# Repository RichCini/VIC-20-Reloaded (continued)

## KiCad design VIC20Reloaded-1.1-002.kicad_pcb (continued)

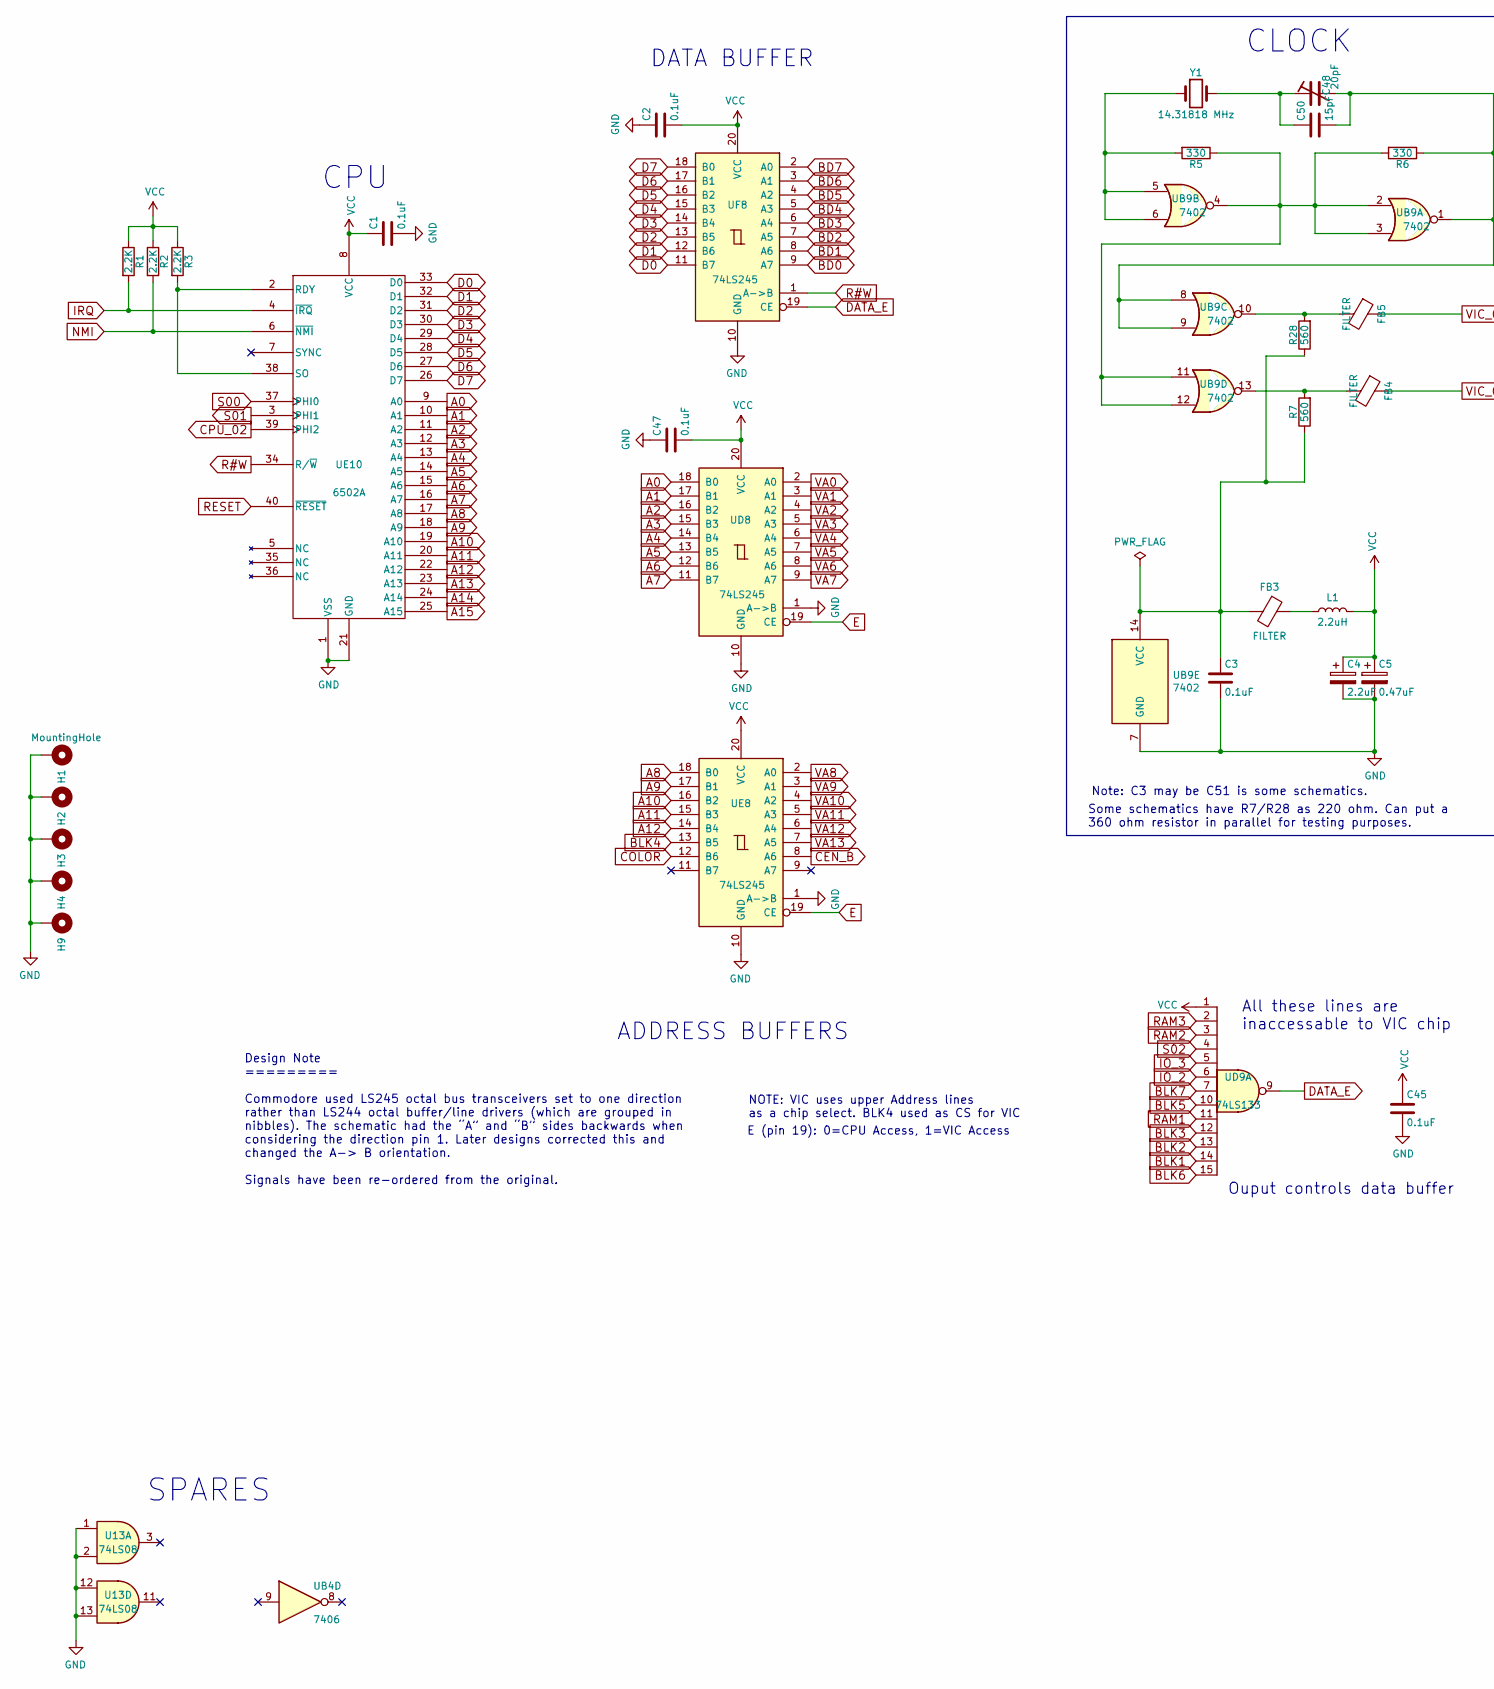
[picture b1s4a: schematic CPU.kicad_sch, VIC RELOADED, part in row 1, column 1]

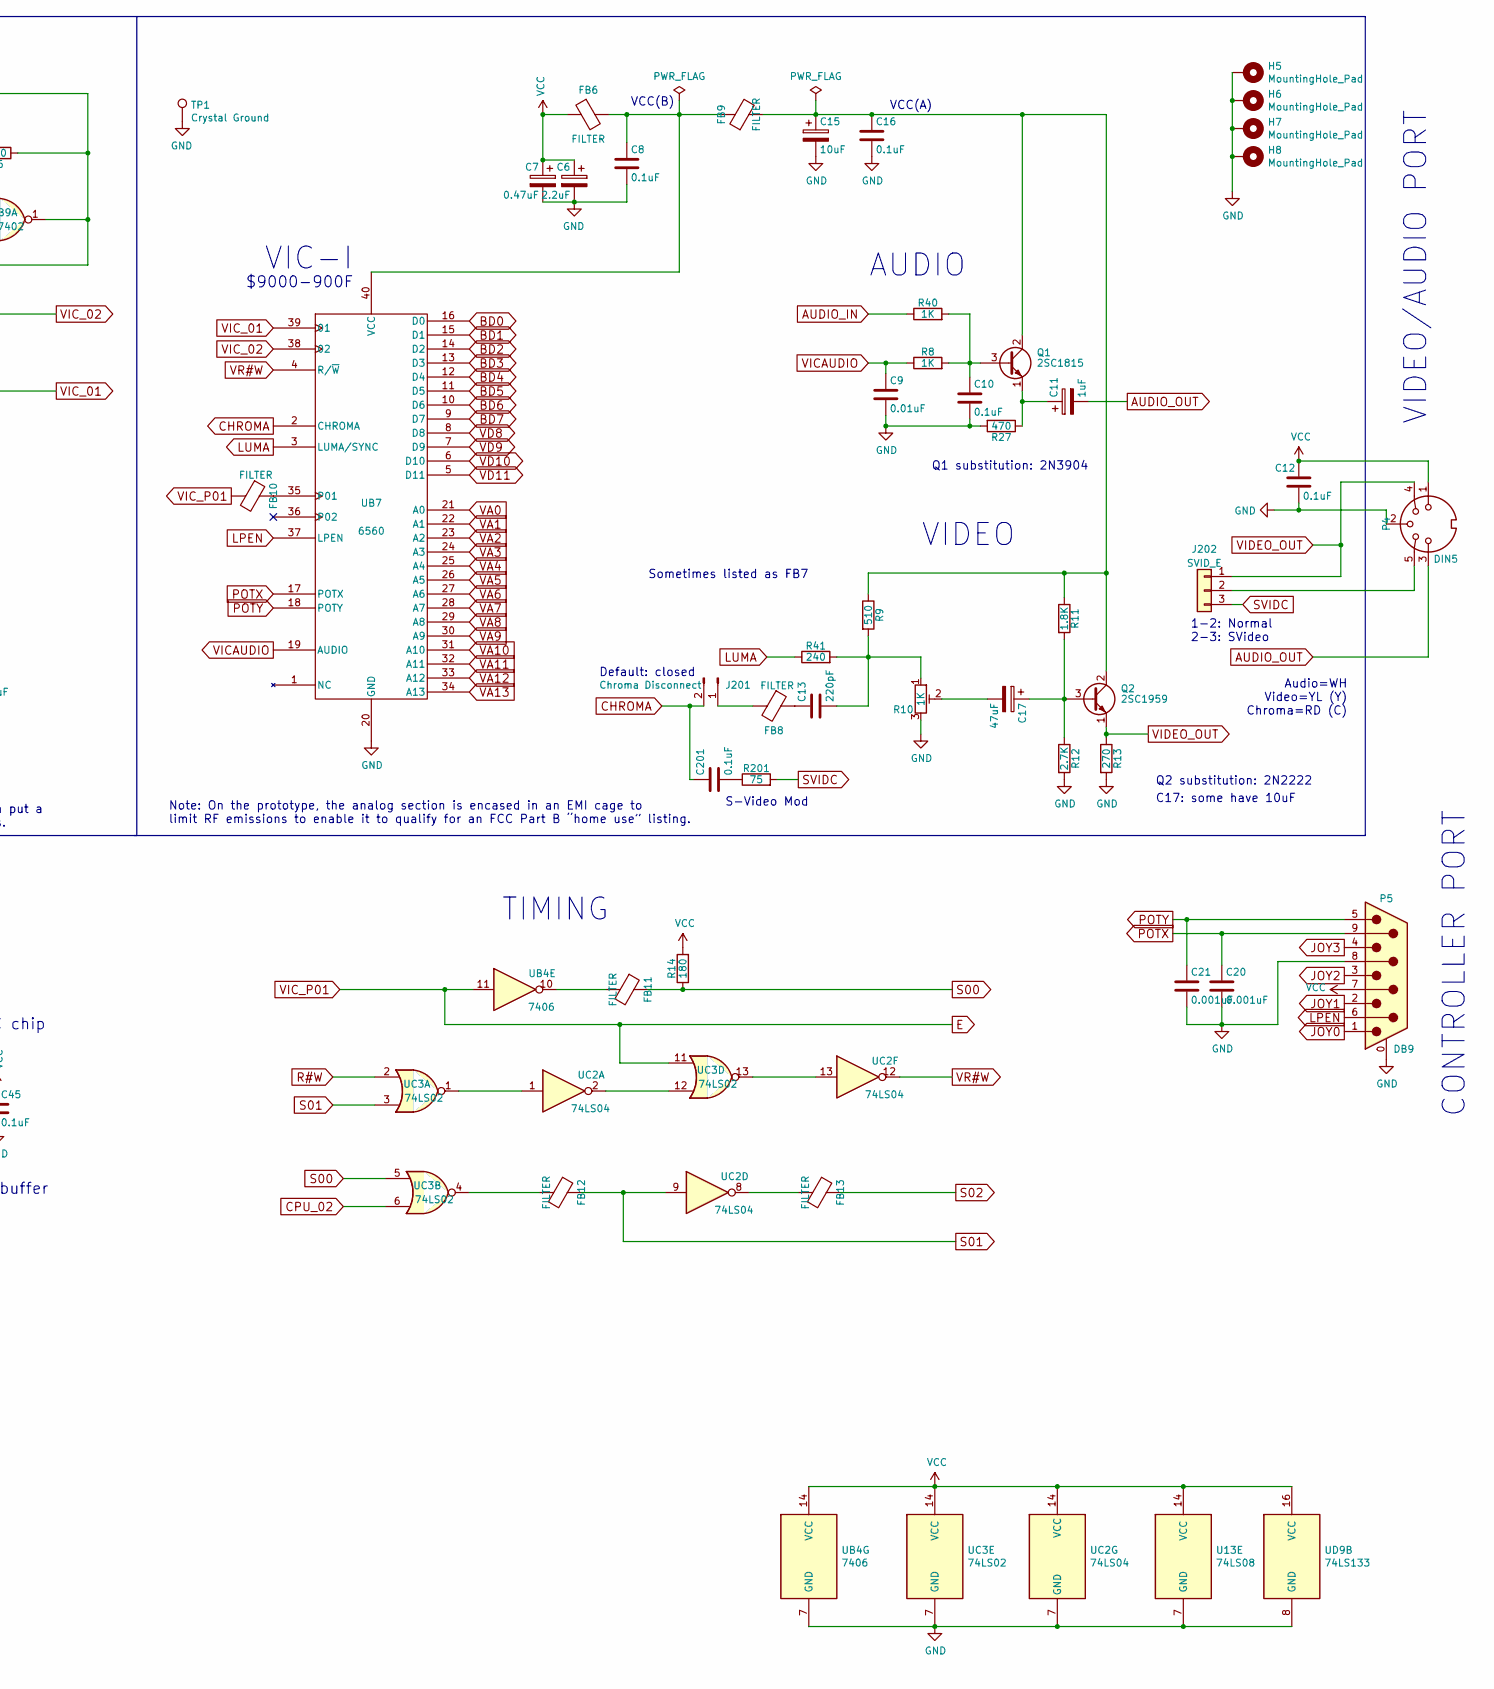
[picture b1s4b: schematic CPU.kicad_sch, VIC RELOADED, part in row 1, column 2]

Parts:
C1, C2, C3, C8, C10, C12, C16, C45, C47, C201: 0.1uF; C_Disc_D4.3mm_W1.9mm_P5.00mm
C4, C6: 2.2uF; CP_Radial_D5.0mm_P2.50mm
C5, C7: 0.47uF; CP_Radial_D5.0mm_P2.50mm
C9: 0.01uF; C_Disc_D4.3mm_W1.9mm_P5.00mm
C11: 1uF; CP_Radial_D4.0mm_P1.50mm
C13: 220pF; C_Disc_D4.3mm_W1.9mm_P5.00mm
C15: 10uF; CP_Radial_D4.0mm_P1.50mm
C17: 47uF; CP_Radial_D5.0mm_P2.00mm
C20, C21: 0.001uF; C_Disc_D4.3mm_W1.9mm_P5.00mm
C48: 20pF; C_Radial_D10.0mm_H12.5mm_P5.00mm
C50: 15pF; C_Disc_D4.3mm_W1.9mm_P5.00mm
FB3, FB6, FB10, FB12, FB13: FILTER; L_Axial_L7.0mm_D3.3mm_P10.16mm_Horizontal_Fastron_MICC
FB4, FB5, FB8, FB9, FB11: FILTER; L_Axial_L7.0mm_D3.3mm_P2.54mm_Vertical_Fastron_MICC
H1, H2, H3, H4, H9: MountingHole; MountingHole_3.2mm_M3_DIN965_Pad
H5, H6, H7, H8: MountingHole_Pad; MountingHole_2.2mm_M2_Pad
J201: Chroma Disconnect; PinHeader_2x01_P2.54mm_Vertical
J202: SVID_E; PinHeader_1x03_P2.54mm_Vertical
L1: 2.2uH; L_Axial_L7.0mm_D3.3mm_P10.16mm_Horizontal_Fastron_MICC
P4: DIN5; CUI_SDS-50J
P5: DB9; DSUB-9_Male_Horizontal_P2.77x2.84mm_EdgePinOffset7.70mm_Hou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
Q1: 2SC1815; TO-92
Q2: 2SC1959; TO-92
R1, R2, R3: 2.2K; R_Axial_DIN0207_L6.3mm_D2.5mm_P7.62mm_Horizontal
R5, R6: 330; R_Axial_DIN0207_L6.3mm_D2.5mm_P2.54mm_Vertical
R7, R28: 560; R_Axial_DIN0207_L6.3mm_D2.5mm_P2.54mm_Vertical
R8, R40: 1K; R_Axial_DIN0207_L6.3mm_D2.5mm_P2.54mm_Vertical
R9: 510; R_Axial_DIN0207_L6.3mm_D2.5mm_P2.54mm_Vertical
R10: 1K; Potentiometer_Bourns_3266W_Vertical
R11: 1.8K; R_Axial_DIN0207_L6.3mm_D2.5mm_P2.54mm_Vertical
R12: 2.7K; R_Axial_DIN0207_L6.3mm_D2.5mm_P2.54mm_Vertical
R13: 270; R_Axial_DIN0207_L6.3mm_D2.5mm_P2.54mm_Vertical
R14: 180; R_Axial_DIN0207_L6.3mm_D2.5mm_P7.62mm_Horizontal
R27: 470; R_Axial_DIN0207_L6.3mm_D2.5mm_P2.54mm_Vertical
R41: 240; R_Axial_DIN0207_L6.3mm_D2.5mm_P2.54mm_Vertical
R201: 75; R_Axial_DIN0207_L6.3mm_D2.5mm_P2.54mm_Vertical
TP1: Crystal Ground; TestPoint_THTPad_D1.0mm_Drill0.5mm
U13: 74LS08; DIP-14_W7.62mm_Socket
UB4: 7406; DIP-14_W7.62mm_Socket
UB7: 6560; DIP-40_W15.24mm_Socket
UB9: 7402; DIP-14_W7.62mm_Socket
UC2: 74LS04; DIP-14_W7.62mm_Socket
UC3: 74LS02; DIP-14_W7.62mm_Socket
UD8: 74LS245; DIP-20_W7.62mm_Socket
UD9: 74LS133; DIP-16_W7.62mm_Socket
UE8: 74LS245; DIP-20_W7.62mm_Socket
UE10: 6502A; DIP-40_W15.24mm_Socket
UF8: 74LS245; DIP-20_W7.62mm_Socket
Y1: 14.31818 MHz; Crystal_HC18-U_Vertical

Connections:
A0: UD8.18 (B0), UE10.9 (A0); also elsewhere on the board
A1: UD8.17 (B1), UE10.10 (A1); also elsewhere on the board
A2: UD8.16 (B2), UE10.11 (A2); also elsewhere on the board
A3: UD8.15 (B3), UE10.12 (A3); also elsewhere on the board
A4: UD8.14 (B4), UE10.13 (A4); also elsewhere on the board
A5: UD8.13 (B5), UE10.14 (A5); also elsewhere on the board
A6: UD8.12 (B6), UE10.15 (A6); also elsewhere on the board
A7: UD8.11 (B7), UE10.16 (A7); also elsewhere on the board
A8: UE8.18 (B0), UE10.17 (A8); also elsewhere on the board
A9: UE8.17 (B1), UE10.18 (A9); also elsewhere on the board
A10: UE8.16 (B2), UE10.19 (A10); also elsewhere on the board
A11: UE8.15 (B3), UE10.20 (A11); also elsewhere on the board
A12: UE8.14 (B4), UE10.22 (A12); also elsewhere on the board
A13: UE10.23 (A13); also elsewhere on the board
A14: UE10.24 (A14); also elsewhere on the board
A15: UE10.25 (A15); also elsewhere on the board
AUDIO_IN: R40.1; also elsewhere on the board
AUDIO_OUT: C11.2, P4.3
BD0: UB7.16 (D0), UF8.9 (A7); also elsewhere on the board
BD1: UB7.15 (D1), UF8.8 (A6); also elsewhere on the board
BD2: UB7.14 (D2), UF8.7 (A5); also elsewhere on the board
BD3: UB7.13 (D3), UF8.6 (A4); also elsewhere on the board
BD4: UB7.12 (D4), UF8.5 (A3); also elsewhere on the board
BD5: UB7.11 (D5), UF8.4 (A2); also elsewhere on the board
BD6: UB7.10 (D6), UF8.3 (A1); also elsewhere on the board
BD7: UB7.9 (D7), UF8.2 (A0); also elsewhere on the board
BLK1: UD9.14; also elsewhere on the board
BLK2: UD9.13; also elsewhere on the board
BLK3: UD9.12; also elsewhere on the board
BLK4: UE8.13 (B5); also elsewhere on the board
BLK5: UD9.10; also elsewhere on the board
BLK6: UD9.15; also elsewhere on the board
BLK7: UD9.7; also elsewhere on the board
CEN_B: UE8.8 (A6); also elsewhere on the board
CHROMA: C201.1, J201.2, UB7.2 (CHROMA)
COL7: P5.4; also elsewhere on the board
COLOR: UE8.12 (B6); also elsewhere on the board
CPU_02: UC3.6, UE10.39 (PHI2)
D0: UE10.33 (D0), UF8.11 (B7); also elsewhere on the board
D1: UE10.32 (D1), UF8.12 (B6); also elsewhere on the board
D2: UE10.31 (D2), UF8.13 (B5); also elsewhere on the board
D3: UE10.30 (D3), UF8.14 (B4); also elsewhere on the board
D4: UE10.29 (D4), UF8.15 (B3); also elsewhere on the board
D5: UE10.28 (D5), UF8.16 (B2); also elsewhere on the board
D6: UE10.27 (D6), UF8.17 (B1); also elsewhere on the board
D7: UE10.26 (D7), UF8.18 (B0); also elsewhere on the board
DATA_E: UD9.9, UF8.19 (CE)
E: FB10.2, UB4.11, UC3.11, UD8.19 (CE), UE8.19 (CE)
GND: C1.2, C2.1, C3.2, C4.2, C5.2, C6.2, C7.2, C8.2, C9.2, C10.2, C12.2, C15.2, C16.2, C20.2, C21.2, C45.2, C47.1, H1.1, H2.1, H3.1, H4.1, H5.1, H6.1, H7.1, H8.1, H9.1, P4.2, P5.0 (PAD), P5.8, R10.3, R12.2, R13.2, R27.2, TP1.1, U13.1, U13.2, U13.7 (GND), U13.12, U13.13, UB4.7 (GND), UB7.20 (GND), UB9.7 (GND), UC2.7 (GND), UC3.7 (GND), UD8.1 (A->B), UD8.10 (GND), UD9.8 (GND), UE8.1 (A->B), UE8.10 (GND), UE10.1 (VSS), UE10.21 (GND), UF8.10 (GND); also elsewhere on the board
IO_2: UD9.6; also elsewhere on the board
IO_3: UD9.5; also elsewhere on the board
IRQ: R1.2, UE10.4 (~IRQ); also elsewhere on the board
JOY0: P5.1; also elsewhere on the board
JOY1: P5.2; also elsewhere on the board
JOY2: P5.3; also elsewhere on the board
LPEN: P5.6, UB7.37 (LPEN); also elsewhere on the board
LUMA: R41.1, UB7.3 (LUMA/SYNC)
NMI: R2.2, UE10.6 (~NMI); also elsewhere on the board
unnamed: C3.1, FB3.2, R7.1, R28.1, UB9.14 (VCC)
unnamed: C8.1, FB6.2, FB9.1, UB7.40 (VCC)
unnamed: C10.1, Q1.3 (B), R8.2, R40.2
unnamed: C11.1, Q1.1 (E), R27.1
unnamed: C13.1, FB8.1
unnamed: C13.2, R9.2, R10.1, R41.2
unnamed: C15.1, C16.1, FB9.2, Q1.2 (C), Q2.2 (C), R9.1, R11.1
unnamed: C17.1, Q2.3 (B), R11.2, R12.1
unnamed: C17.2, R10.2
unnamed: C48.1, C50.1, Y1.2
unnamed: C48.2, C50.2, R6.1, UB9.1, UB9.8, UB9.9
unnamed: C201.2, R201.1
unnamed: FB3.1, L1.1
unnamed: FB4.2, R7.2, UB9.13
unnamed: FB5.2, R28.2, UB9.10
unnamed: FB8.2, J201.1
unnamed: FB10.1, UB7.35 (P01)
unnamed: FB11.2, UB4.10
unnamed: FB12.2, UC3.4
unnamed: FB13.2, UC2.8
unnamed: J202.2, P4.5
unnamed: R3.2, UE10.2 (RDY), UE10.38 (SO)
unnamed: R5.1, R6.2, UB9.2, UB9.3, UB9.4, UB9.11, UB9.12
unnamed: R5.2, UB9.5, UB9.6, Y1.1
unnamed: UC2.1, UC3.1
unnamed: UC2.2, UC3.12
unnamed: UC2.13, UC3.13
POTX: C20.1, P5.9, UB7.17 (POTX)
POTY: C21.1, P5.5, UB7.18 (POTY)
R#W: UC3.2, UE10.34 (R/~W), UF8.1 (A->B); also elsewhere on the board
RAM1: UD9.11; also elsewhere on the board
RAM2: UD9.3; also elsewhere on the board
RAM3: UD9.2; also elsewhere on the board
RESET: UE10.40 (~RESET); also elsewhere on the board
S00: FB11.1, R14.1, UC3.5, UE10.37 (PHI0)
S01: FB12.1, UC2.9, UC3.3, UE10.3 (PHI1); also elsewhere on the board
S02: FB13.1, UD9.4; also elsewhere on the board
SVIDC: J202.3, R201.2
VA0: UB7.21 (A0), UD8.2 (A0); also elsewhere on the board
VA1: UB7.22 (A1), UD8.3 (A1); also elsewhere on the board
VA2: UB7.23 (A2), UD8.4 (A2); also elsewhere on the board
VA3: UB7.24 (A3), UD8.5 (A3); also elsewhere on the board
VA4: UB7.25 (A4), UD8.6 (A4); also elsewhere on the board
VA5: UB7.26 (A5), UD8.7 (A5); also elsewhere on the board
VA6: UB7.27 (A6), UD8.8 (A6); also elsewhere on the board
VA7: UB7.28 (A7), UD8.9 (A7); also elsewhere on the board
VA8: UB7.29 (A8), UE8.2 (A0); also elsewhere on the board
VA9: UB7.30 (A9), UE8.3 (A1); also elsewhere on the board
VA10: UB7.31 (A10), UE8.4 (A2); also elsewhere on the board
VA11: UB7.32 (A11), UE8.5 (A3); also elsewhere on the board
VA12: UB7.33 (A12), UE8.6 (A4); also elsewhere on the board
VA13: UB7.34 (A13), UE8.7 (A5); also elsewhere on the board
VCC: C1.1, C2.2, C4.1, C5.1, C6.1, C7.1, C12.1, C45.1, C47.2, FB6.1, L1.2, P4.1, P5.7, R1.1, R2.1, R3.1, R14.2, U13.14 (VCC), UB4.14 (VCC), UC2.14 (VCC), UC3.14 (VCC), UD8.20 (VCC), UD9.1, UD9.16 (VCC), UE8.20 (VCC), UE10.8 (VCC), UF8.20 (VCC); also elsewhere on the board
VD8: UB7.8 (D8); also elsewhere on the board
VD9: UB7.7 (D9); also elsewhere on the board
VD10: UB7.6 (D10); also elsewhere on the board
VD11: UB7.5 (D11); also elsewhere on the board
VICAUDIO: C9.1, R8.1, UB7.19 (AUDIO)
VIC_01: FB4.1, UB7.39 (01)
VIC_02: FB5.1, UB7.38 (02)
VIDEO_OUT: J202.1, P4.4, Q2.1 (E), R13.1
VR#W: UB7.4 (R/~W), UC2.12; also elsewhere on the board

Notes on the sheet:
CLOCK
$9000-900F
TIMING
VCC(B)
Default: closed
CPU
Ouput controls data buffer
Note: C3 may be C51 is some schematics.
VIC-I
SPARES
VIDEO
VCC(A)
NOTE: VIC uses upper Address lines as a chip select. BLK4 used as CS for VIC
1-2: Normal 2-3: SVideo
AUDIO
Sometimes listed as FB7
Q1 substitution: 2N3904
ADDRESS BUFFERS
E (pin 19): 0=CPU Access, 1=VIC Access
DATA BUFFER
All these lines are inaccessable to VIC chip
C17: some have 10uF
Q2 substitution: 2N2222
S-Video Mod
VIDEO/AUDIO PORT
Audio=WH Video=YL (Y) Chroma=RD (C)
Note: On the prototype, the analog section is encased in an EMI cage to limit RF emissions to enable it to qualify for an FCC Part B “home use” listing.
Design Note ========= Commodore used LS245 octal bus transceivers set to one direction rather than LS244 octal buffer/line drivers (which are grouped in nibbles). The schematic had the “A” and “B” sides backwards when considering the direction pin 1. Later designs corrected this and changed the A->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
Some schematics have R7/R28 as 220 ohm. Can put a 360 ohm resistor in parallel for testing purposes.
CONTROLLER PORT

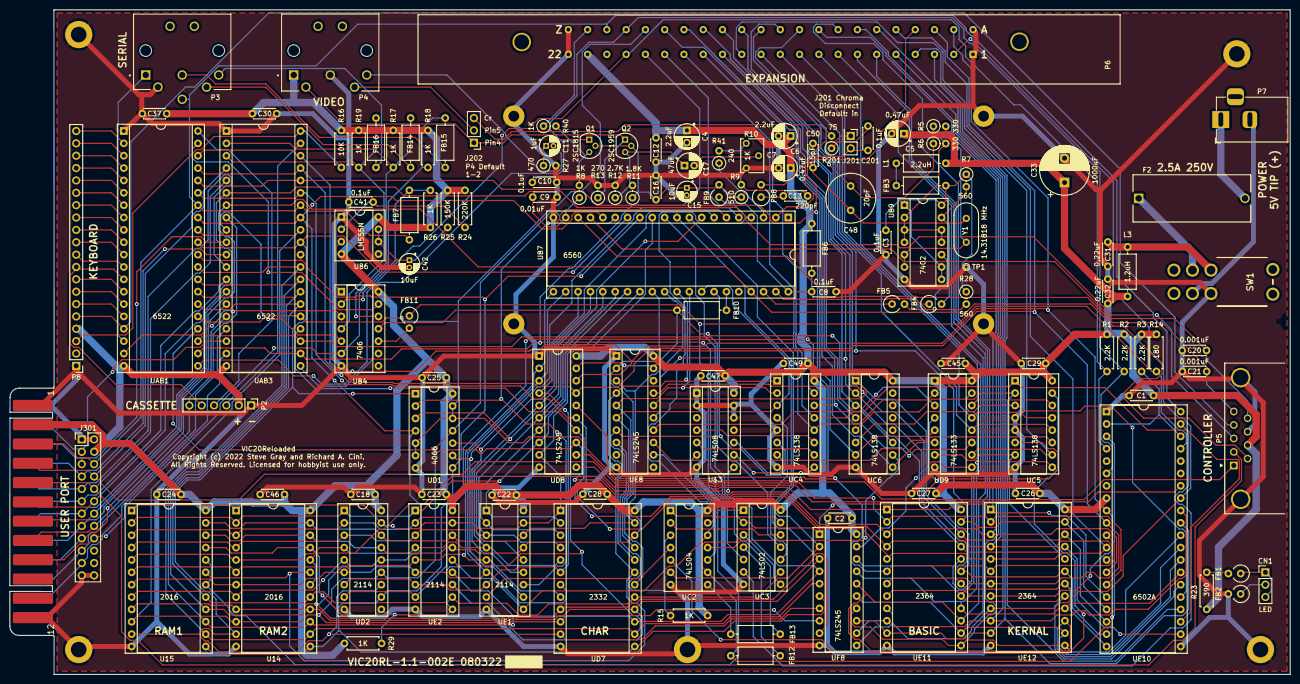
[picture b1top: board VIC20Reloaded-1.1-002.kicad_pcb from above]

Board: 2 copper layers, 263.1 x 136.6 mm, 140 parts (1 on the bottom side), 183 nets.

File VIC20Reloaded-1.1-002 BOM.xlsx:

Item | Qty | Reference(s) | Value | Description | Footprint | Mouser Part Number
1 | 23 | C1, C2, C3, C8, C10, C12, C16, C18, C22, C23, C24, C25, C26, C27, C28, C29, C30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 | 0.1uF 50v X7R | Bypass capacitor 5mm | Capacitor_THT:C_Disc_D4.3mm_W1.9mm_P5.00mm | K104K15X7RF53H5
2 | 2 | C4, C6 | 2.2uF 25v | Tantalum 4x1.5mm | Capacitor_THT:CP_Radial_D4.0mm_P1.50mm | TAP225K035CRW
3 | 2 | C5, C7 | 0.47uF 50v | Tantalum 4x1.5mm | Capacitor_THT:CP_Radial_D4.0mm_P1.50mm | TAP474K035CRW
4 | 1 | C9 | 0.01uF | MLCC | Capacitor_THT:C_Disc_D4.3mm_W1.9mm_P5.00mm
5 | 1 | C11 | 1uF 50v | Electrolytic 4x1.5mm | Capacitor_THT:CP_Radial_D4.0mm_P1.50mm | UMA1H010MDD
6 | 1 | C13 | 220pF 50v | MLCC | Capacitor_THT:C_Disc_D4.3mm_W1.9mm_P5.00mm | FG28C0G1H221JNT06
7 | 2 | C15, C42 | 10uF 50v | Electrolytic 4x1.5mm | Capacitor_THT:CP_Radial_D4.0mm_P1.50mm | 50ML10MEFC5X7
8 | 1 | C17 | 47uF 25v | Tantalum 4x1.5mm | Capacitor_THT:CP_Radial_D4.0mm_P1.50mm
9 | 2 | C20, C21 | 0.001uF 50v | MLCC | Capacitor_THT:C_Disc_D4.3mm_W1.9mm_P5.00mm
10 | 2 | C31, C32 | 0.22uF 50v | MLCC | Capacitor_THT:C_Disc_D4.3mm_W1.9mm_P5.00mm
11 | 1 | C33 | 1000uF, 16v | Electrolytic 10x16x5mm | Capacitor_THT:CP_Radial_D10.0mm_P5.00mm
12 | 1 | C34 | 2200uF, 16v Alt | Electrolytic 10x16x5mm | Capacitor_THT:CP_Radial_D10.0mm_P5.00mm | 80-A750MW228M1CAAE10
13 | 1 | C48 | 20pF 100v | trimmer cap (red) 6-30pF | Capacitor_THT:C_Radial_D10.0mm_H12.5mm_P5.00mm | GKG30015
14 | 1 | C50 | 15pF 50v | ceramic | Capacitor_THT:C_Disc_D4.3mm_W1.9mm_P5.00mm | FG28C0G1H150JNT06
15 | 1 | CN1 | CONN_01X03 | 1x3 0.1" header/power LED | Connector_PinHeader_2.54mm:PinHeader_1x03_P2.54mm_Vertical
16 | 1 | F1 | 250mA fuse, TE5 |  | Littlefuse 250mA 5.08mm PC mount (mount with holder) | 576-39502500440
17 | 1 | F1X | Fuse holder, TE5 |  | Littlefuse TE5/TR5 holder | 576-56200001009
18 | 1 | F2 | 2.5A 5mm FB fuse |  | standard 5x20mm fuse | 530-5SF2.5-R
19 | 1 | F2X | 5mm fuse holder |  | Fuse holder, Keystone 4527 | 534-4527
20 | 1 | F2X1 | fuse holder cover |  | Fuse holder, Keystone 4527 cover | 534-4527C
21 | 7 | FB1, FB2, FB4, FB5, FB8, FB9, FB11 | FILTER | ferrite bead, Fair-Rite | Inductor_THT:L_Axial_L7.0mm_D3.3mm_P2.54mm_Vertical | 2743001112
22 | 9 | FB3, FB6, FB7, FB10, FB12, FB13, FB14, FB15, FB16 | FILTER | ferrite bead, Fair-Rite | Inductor_THT:L_Axial_L7.0mm_D3.3mm_P10.16mm_Horizontal | 2743001112
23 | 1 | L1 | 2.2uH | inductor, Bourns | Inductor_THT:L_Axial_L7.0mm_D3.3mm_P10.16mm_Horizontal | 78F2R2K-RC
24 | 1 | L3 | 1.2uH | inductor, TDK | Inductor_THT:L_Axial_L7.0mm_D3.3mm_P10.16mm_Horizontal | B82144F2122K000
25 | 1 | P1 | CONN_02X12 | 2x12 0.1" header USERP | Connector_PinHeader_2.54mm:PinHeader_2x12_P2.54mm_Vertical
26 | 1 | P2 | CASSETTE | 1x6 0.1" header CASS | Connector_PinHeader_2.54mm:PinHeader_1x06_P2.54mm_Vertical
27 | 1 | P3 | DIN6 | DIN6 Serial IEC |  | SDS-60J
28 | 1 | P4 | DIN5 | DIN5 Video |  | SDS-50J
29 | 1 | P5 | DE9M | DE9M/joystick | Connector_Dsub:DSUB-9_Male_Horizontal_P2.77x2.84mm_EdgePinOffset7.70mm_Housed_M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 | ID09P33E4GX00LF
30 | 1 | P6 | EXPANSION | 2x22 R/A card connector | EDAC. Can be vertical or R/A depending on need (R/A specified) | 307-044-558-201
31 | 1 | P6 alternate | EXPANSION | 2x22 card connector | EDAC. Can be vertical or R/A depending on need (R/A specified) | 307-044-524-202
32 | 1 | P7 | POWER TIP+ | barrel jack | Connector_BarrelJack:BarrelJack_Horizontal | PJ-002AH
33 | 1 | P8 | CONN_01X20 | 1x20 0.1" header KEYB | Connector_PinHeader_2.54mm:PinHeader_1x20_P2.54mm_Vertical
34 | 1 | Q1 | 2SC1815 | transistor | Can substitute 2N2222 | N/A
35 | 1 | Q2 | 2SC1959 | transistor | Can substitute 2N2222 | N/A
36 | 3 | R1, R2, R3 | 2.2KQ | resistor, 1/4w
37 | 2 | R5, R6 | 330Q | resistor, 1/4w
38 | 2 | R7, R28 | 560Q | resistor, 1/4w
39 | 2 | R8, R40 | 1.0KQ | resistor, 1/4w
40 | 1 | R9 | 510KQ | resistor, 1/4w
41 | 1 | R10 | 1.0K vertical POT | trimmer, vertical Bourns 3266W |  | 3266W-1-102LF
42 | 1 | R11 | 1.8KQ | resistor, 1/4w
43 | 1 | R12 | 2.7KQ | resistor, 1/4w
44 | 1 | R13 | 270Q | resistor, 1/4w
45 | 1 | R14 | 180Q | resistor, 1/4w
46 | 6 | R15, R17, R18, R19, R26, R29 | 1.0KQ | resistor, 1/4w
47 | 1 | R16 | 10.0KQ | resistor, 1/4w
48 | 1 | R23 | 390Q | resistor, 1/4w
49 | 1 | R24 | 220KQ | resistor, 1/4w
50 | 1 | R25 | 150KQ | resistor, 1/4w
51 | 1 | R27 | 470Q | resistor, 1/4w
52 | 1 | R41 | 240Q | resistor, 1/4w
53 | 1 | SW1 | Switch, DPDT vertical | power | Mouser-Samec:M2022TXW41DA | 633-M2022TXW41-DA
54 | 1 | U13 | 74LS08 | Quad 2-in AND, OC |  | SN74LS08
55 | 2 | U14, U15 | 2016/6116 SRAM | RAM |  | N/A
56 | 2 | UAB1, UAB3 | R6522 VIA | VIA |  | N/A
57 | 1 | UB4 | 74LS06 | Hex inverter/buffer OC |  | SN74LS06
58 | 1 | UB6 | LM555N | timer |  | LM555CN
59 | 1 | UB7 | 6560 VIC-I | video |  | N/A
60 | 1 | UB9 | 7402 | Quad 2-in positive NOR |  | eBay
61 | 1 | UC2 | 74LS04 | Hex inverter |  | SN74LS04
62 | 1 | UC3 | 74LS02 | Quad 2-in positive NOR |  | SN74LS02
63 | 3 | UC4, UC5, UC6 | 74LS138 | 3-8 decoder/demux |  | SN74LS138
64 | 1 | UD1 | CD4066 | quad switch |  | CD4066BE
65 | 3 | UD2, UE1, UE2 | 2114AL-3 | 1kx4 SRAM |  | N/A
66 | 1 | UD7 | 2332 mask ROM | character ROM |  | N/A
67 | 3 | UD8, UE8, UF8 | 74LS245 | Octal bus transciever, tri-state |  | SN74LS245
68 | 1 | UD9 | 74LS133 | 13-input NAND |  | SN74LS133
69 | 1 | UE10 | 6502A | CPU |  | N/A
70 | 2 | UE11, UE12 | 2364 mask ROM | BASIC/KERNAL |  | N/A
71 | 1 | Y1 | 14.31818 MHz XTAL | must be series capacitance | Crystal:Crystal_HC49-U_Vertical | ECS-143-S-1X | CTX088
72 | 1 |  | DIP8 | dual-wipe socket, crimp pin |  | 4808-3004-CP
73 | 6 |  | DIP14 | dual-wipe socket, crimp pin |  | 4814-3004-CP
74 | 4 |  | DIP16 | dual-wipe socket, crimp pin |  | 4816-3004-CP
75 | 3 |  | DIP18 | dual-wipe socket, crimp pin |  | 4818-3004-CP
76 | 3 |  | DIP20 | dual-wipe socket, crimp pin |  | 4820-3004-CP
77 | 5 |  | DIP24 | dual-wipe socket, crimp pin |  | 4824-6004-CP
78 | 4 |  | DIP40 | dual-wipe socket, crimp pin |  | 4840-6004-CP

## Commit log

2022-06-10 Create temp
2022-08-07 Add files via upload
    Updated to final versions.
2022-08-07 Update README.md
    Updated for 002E final version.
